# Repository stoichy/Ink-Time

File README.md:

# InkTime - Open Source Smartwatch

InkTime is a low-cost, open-source smartwatch designed for the **EVT (Engineering Validation Test)** phase. This project involves the full hardware design cycle, from schematic capture and PCB layout in Autodesk Fusion 360 to mechanical integration and manufacturing file generation.

## Project Overview

The system architecture centers around the **nRF52840** (Nordic Semiconductor) for BLE connectivity and ultra-low power consumption, paired with a high-contrast E-Paper display.

### Key Features
- **MCU:** Nordic nRF52840 (Cortex-M4 + BLE 5.0).
- **Display:** 1.54" E-Paper (Ultra-low power, sunlight readable).
- **Power:** USB-C charging with 180mAh LiPo battery.
- **Form Factor:** Compact design ready for mechanical integration.

---

## System Architecture

### Block Diagram

The core of the device integrates high-speed SPI for the display and I2C for peripheral sensors.

### Hardware Functionality
- **Microcontroller:** The nRF52840 provides a 2.4GHz radio and ARM® Cortex®-M4 processor.
- **Interfaces:**
  - **SPI:** Dedicated for the E-Ink display to ensure high-speed data transfer.
  - **I2C:** Connects the IMU (Inertial Measurement Unit) and Fuel Gauge for battery monitoring.
  - **GPIO:** Used for tactile buttons and the haptic shaker motor (PWM controlled).
- **Power System:** Charged via USB-C (5V), regulated to 3.3V via a low-dropout (LDO) regulator.

---

## Bill of Materials (BOM)

| Component | Value/Model | Package | Provider (JLC) | Datasheet |
| :--- | :--- | :--- | :--- | :--- |
| **MCU** | nRF52840a | QFN™73 | [JLC Part](https://jlcpcb.com/) | [Link](https://infocenter.nordicsemi.com/pdf/nRF52840_PS_v1.1.pdf) |
| **Display** | E-Paper 1.54" | FPC | [JLC Part](https://jlcpcb.com/) | [Link](#) |
| **Charger IC** | MCP73832 | SOT-23-5 | [JLC Part](https://jlcpcb.com/) | [Link](https://ww1.microchip.com/downloads/en/DeviceDoc/20001984g.pdf) |
| **Battery** | LiPo 180mAh | Custom | N/A | [Link](#) |
| **LDO** | 3.3V Regulator | SOT-23 | [JLC Part](https://jlcpcb.com/) | [Link](#) |

---

## Pinout Mapping

| nRF52840 Pin | Function | Description |
| :--- | :--- | :--- |
| **P0.xx** | SPI_SCK | Serial Clock for E-Ink |
| **P0.yy** | SPI_MOSI | Master Out Slave In for E-Ink |
| **P0.zz** | I2C_SDA | Data line for Sensors |
| **P0.ww** | PWM_VIB | Haptic motor control |

---

## Energy Budget

- **Battery Capacity:** 180 mAh.
- **Deep Sleep Mode:** Estimated < 50 µA.
- **Active Refresh:** ~8-12 mA (peak during E-Ink refresh).
- **Estimated Standby:** Approx. 10-14 days.

---

## Design Log & Constraints

### PCB Implementation
- **Layers:** 2-layer design (Top/Bottom) with dedicated ground planes.
- **Trace Widths:** Power (0.3mm), Signal (0.15mm) to comply with JLC manufacturing standards.
- **Decoupling:** 100nF capacitors (0201) placed close to MCU VCC pins.

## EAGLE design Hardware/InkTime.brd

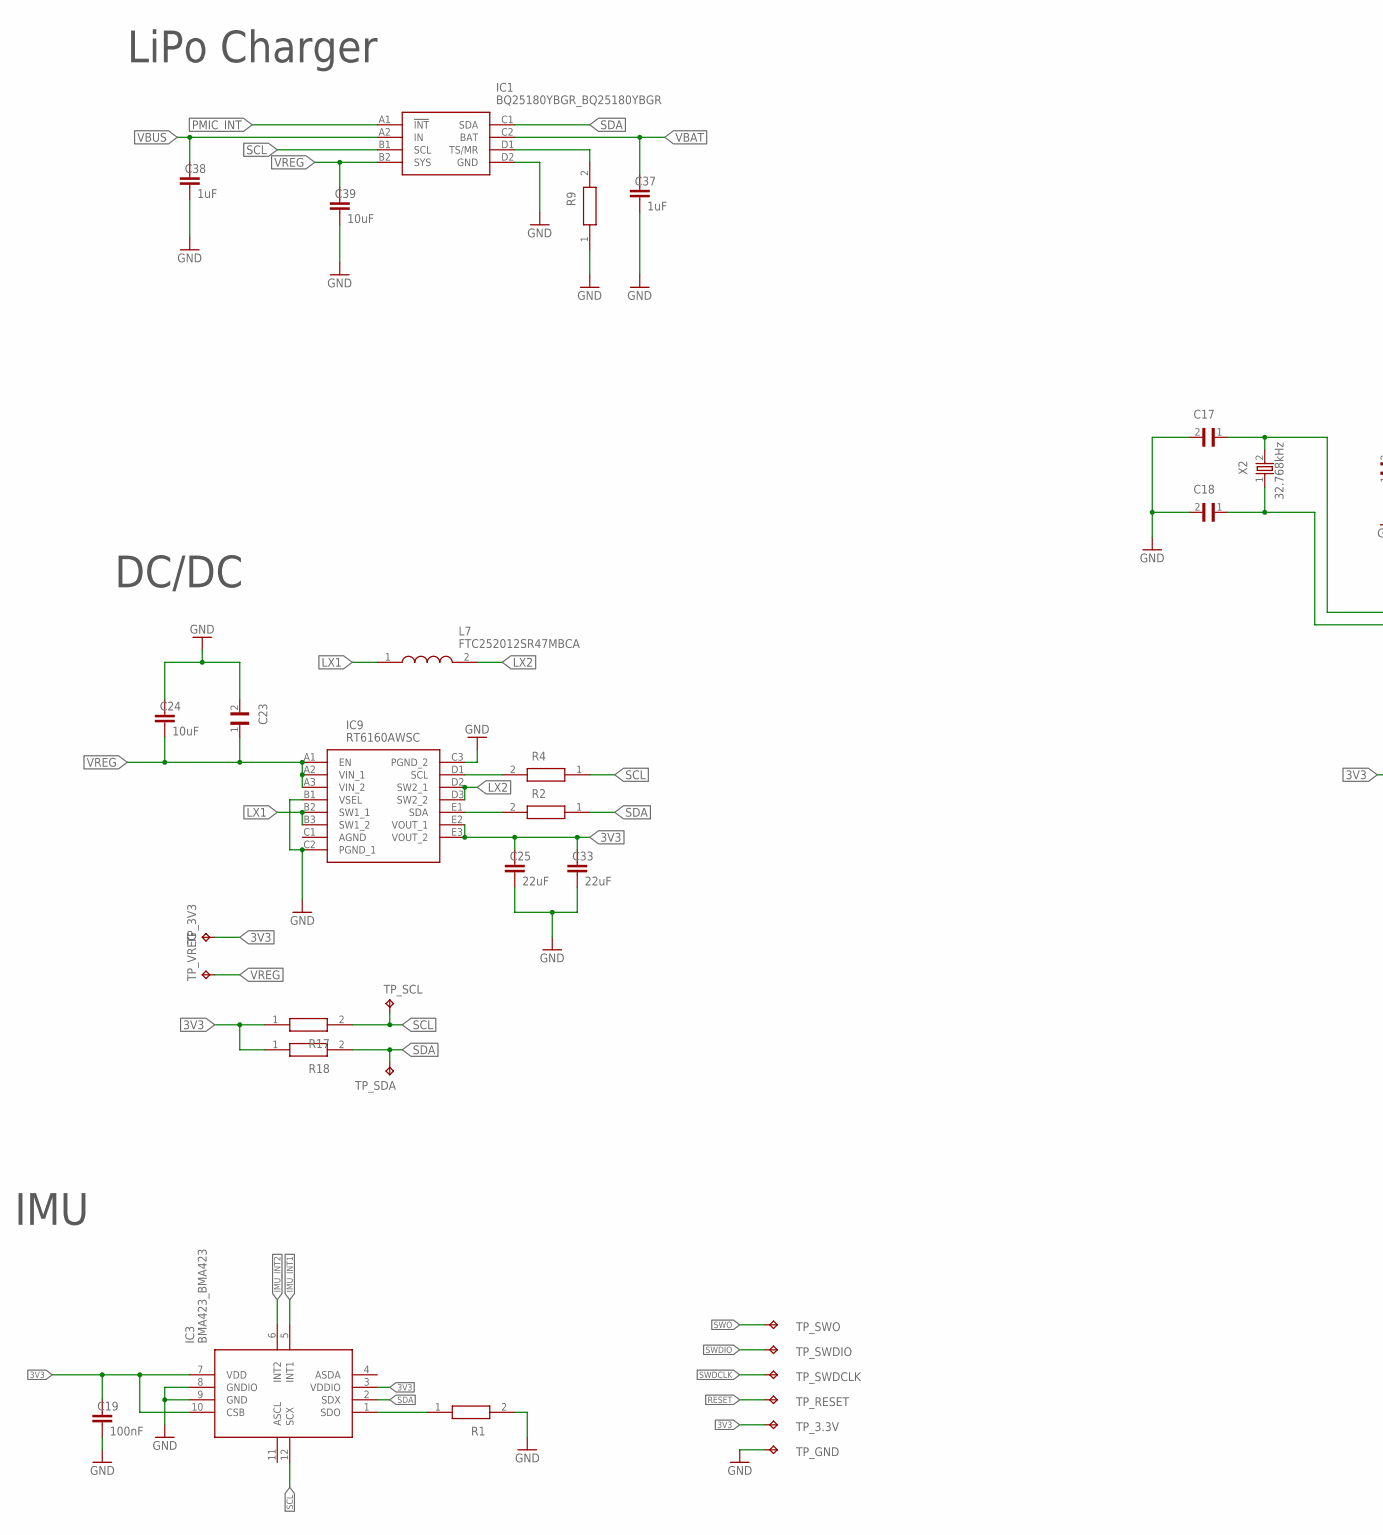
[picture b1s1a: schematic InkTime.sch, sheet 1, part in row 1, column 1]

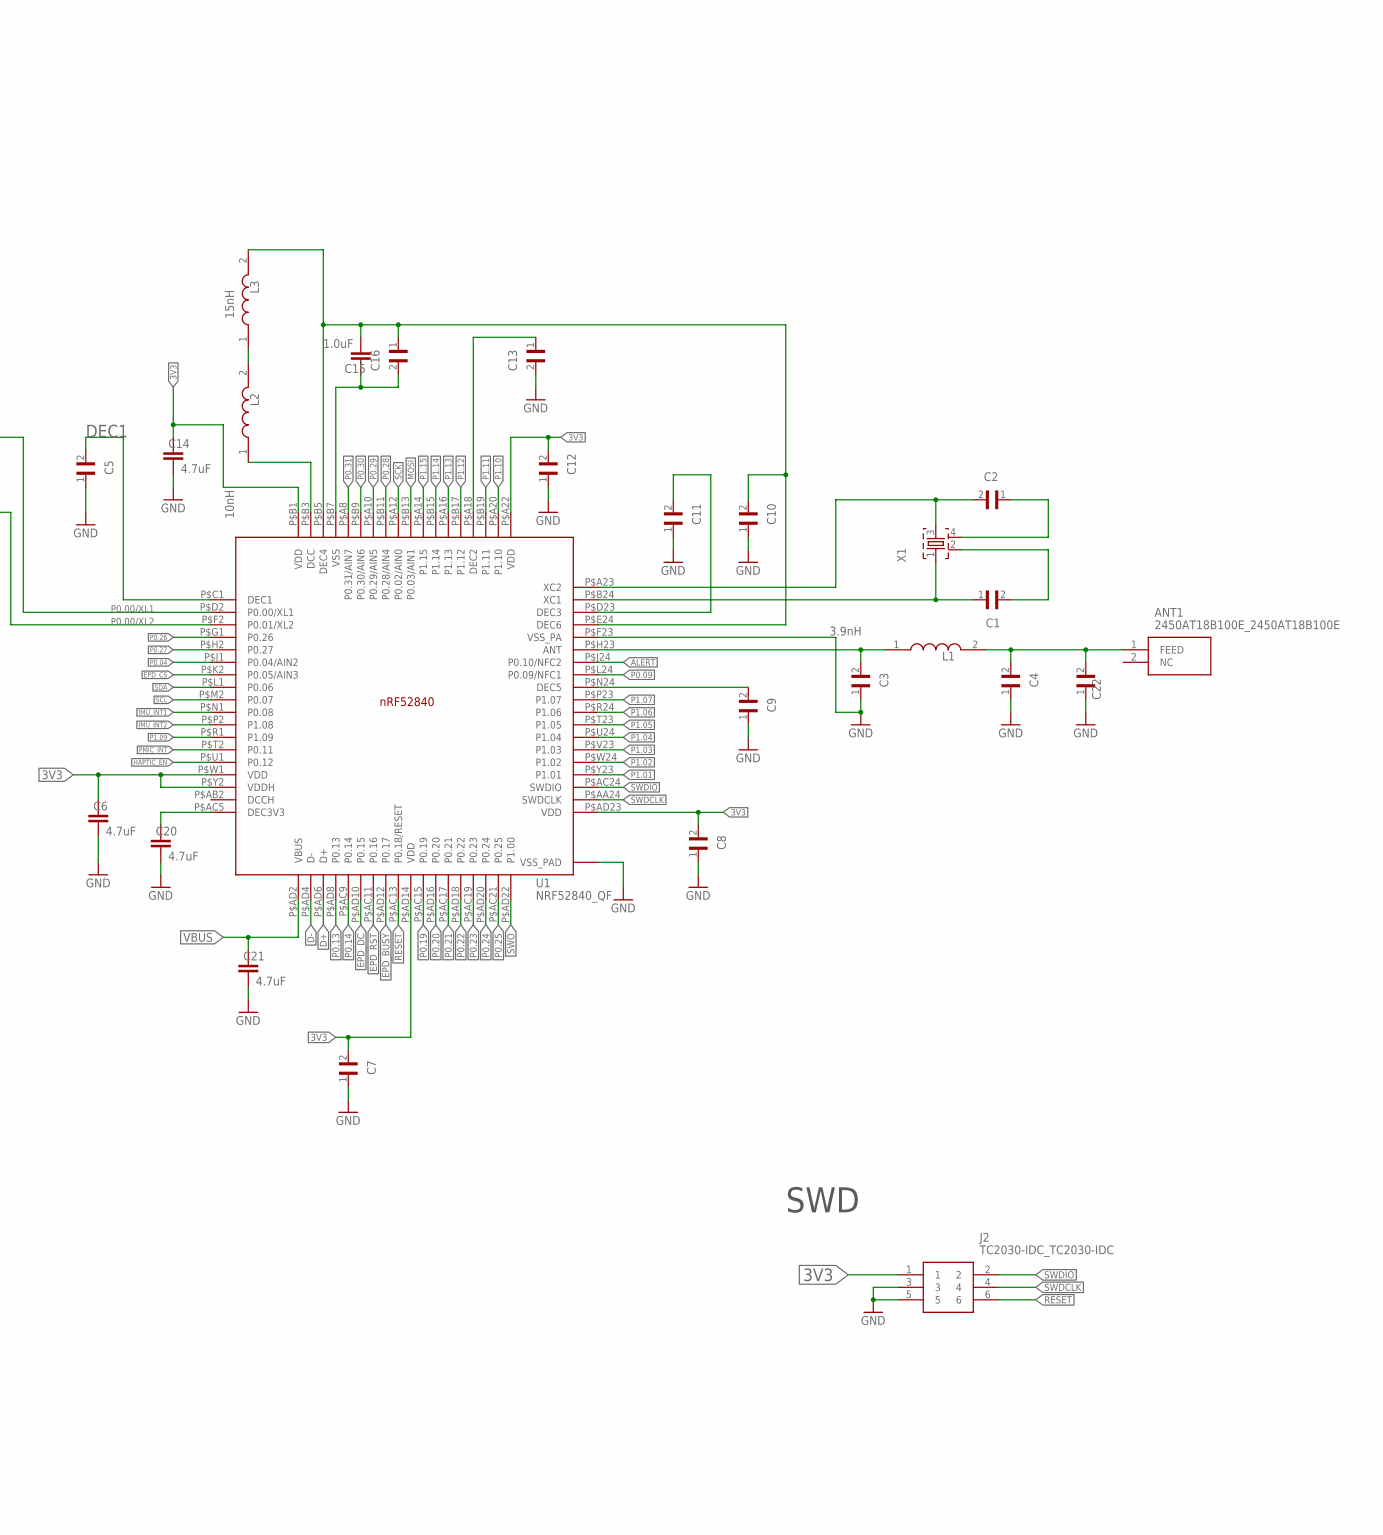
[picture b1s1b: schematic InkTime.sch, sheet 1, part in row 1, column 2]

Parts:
ANT1: 2450AT18B100E_2450AT18B100E; 2450AT18B100E_ANTC3216X140N
C1, C2, C17, C18: 12pF; GRM011R60J152KE01L_2_CAPC0201X13N
C3, C4: 1pF; GRM011R60J152KE01L_2_CAPC0201X13N
C5, C7, C8, C12: 100nF; GRM011R60J152KE01L_2_CAPC0201X13N
C6, C14, C20, C21: 4.7uF; NORDIC_NRF_3_RESC0402_N
C9: 820pF; GRM011R60J152KE01L_2_CAPC0201X13N
C10, C13, C22: N.C.; GRM011R60J152KE01L_2_CAPC0201X13N
C11: 100pF; GRM011R60J152KE01L_2_CAPC0201X13N
C15: 1.0uF; NORDIC_NRF_3_RESC0402_N
C16: 47nF; GRM011R60J152KE01L_2_CAPC0201X13N
C19: 100nF; NORDIC_NRF_3_RESC0402_N
C23: 0.1uF; GRM011R60J152KE01L_2_CAPC0201X13N
C24, C39: 10uF; NORDIC_NRF_3_RESC0402_N
C25, C33: 22uF; NORDIC_NRF_3_RESC0402_N
C37, C38: 1uF; NORDIC_NRF_3_RESC0402_N
IC1: BQ25180YBGR_BQ25180YBGR; BQ25180YBGR_BGA8C40P2X4_100X155X50
IC3: BMA423_BMA423
IC9: RT6160AWSC; RT6160AWSC_BGA15C40P3X5_140X230X60
J2: TC2030-IDC_TC2030-IDC; TC2030-IDC_TC2030IDC
L1: 3.9nH; MLP2016SR47MT0S1_INDC2016X100N
L2: 10nH; MLP2016SR47MT0S1_INDC2016X100N
L3: 15nH; MLP2016SR47MT0S1_INDC2016X100N
L7: FTC252012SR47MBCA; MLP2016SR47MT0S1_INDC2016X100N
R1, R2, R4: 0; ERA-1AEB3401C_0201
R9: 10k; ERA-1AEB3401C_0201
R17: 3k3; ERA-1AEB3401C_0201
R18: 3K3; ERA-1AEB3401C_0201
TP_3.3V, TP_3V3: HECTOR_WATCH_1_TPTP20R; HECTOR_WATCH_1_TP20R
TP_GND: HECTOR_WATCH_1_TPTP20R; HECTOR_WATCH_1_TP20R
TP_RESET: HECTOR_WATCH_1_TPTP20R; HECTOR_WATCH_1_TP20R
TP_SCL: HECTOR_WATCH_1_TPTP20R; HECTOR_WATCH_1_TP20R
TP_SDA: HECTOR_WATCH_1_TPTP20R; HECTOR_WATCH_1_TP20R
TP_SWDCLK: HECTOR_WATCH_1_TPTP20R; HECTOR_WATCH_1_TP20R
TP_SWDIO: HECTOR_WATCH_1_TPTP20R; HECTOR_WATCH_1_TP20R
TP_SWO: HECTOR_WATCH_1_TPTP20R; HECTOR_WATCH_1_TP20R
TP_VREG: HECTOR_WATCH_1_TPTP20R; HECTOR_WATCH_1_TP20R
U1: NRF52840_QF; NORDIC_NRF_4_AQFN50P700X700X85_HS-74N
X1: NORDIC_NRF_XTAL_32MHZ; NORDIC_NRF_BT-XTAL_2016_N
X2: 32.768kHz; NORDIC_NRF_1_XTAL_3215_N

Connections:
3V3: C6.1, C7.2, C8.2, C12.2, C14.1, C19.1, C25.1, C33.1, IC3.3 (VDDIO), IC3.7 (VDD), IC3.10 (CSB), IC9.E2 (VOUT_1), IC9.E3 (VOUT_2), J2.1, R17.1, R18.1, TP_3.3V.TP, TP_3V3.TP, U1.P$A22 (VDD), U1.P$AD14 (VDD), U1.P$AD23 (VDD), U1.P$B1 (VDD), U1.P$W1 (VDD), U1.P$Y2 (VDDH); also elsewhere on the board
ALERT: U1.P$J24 (P0.10/NFC2); also elsewhere on the board
D+: U1.P$AD6 (D+); also elsewhere on the board
D-: U1.P$AD4 (D-); also elsewhere on the board
DEC1: C5.2, U1.P$C1 (DEC1)
EPD_BUSY: U1.P$AD12 (P0.17); also elsewhere on the board
EPD_CS: U1.P$K2 (P0.05/AIN3); also elsewhere on the board
EPD_DC: U1.P$AD10 (P0.15); also elsewhere on the board
EPD_RST: U1.P$AC11 (P0.16); also elsewhere on the board
GND: C3.1, C4.1, C5.1, C6.2, C7.1, C8.1, C9.1, C10.1, C11.1, C12.1, C13.2, C14.2, C17.2, C18.2, C19.2, C20.2, C21.2, C22.1, C23.2, C24.1, C25.2, C33.2, C37.2, C38.2, C39.2, IC1.D2 (GND), IC3.8 (GNDIO), IC3.9 (GND), IC9.B1 (VSEL), IC9.C2 (PGND_1), IC9.C3 (PGND_2), J2.3, J2.5, R1.2, R9.1, TP_GND.TP, U1.P$74 (VSS_PAD), U1.P$75 (VSS_PAD), U1.P$76 (VSS_PAD), U1.P$77 (VSS_PAD), U1.P$78 (VSS_PAD), U1.P$79 (VSS_PAD), U1.P$80 (VSS_PAD), U1.P$81 (VSS_PAD), U1.P$82 (VSS_PAD), U1.P$83 (VSS_PAD), U1.P$84 (VSS_PAD), U1.P$85 (VSS_PAD), U1.P$86 (VSS_PAD), U1.P$87 (VSS_PAD), U1.P$88 (VSS_PAD), U1.P$89 (VSS_PAD), U1.P$90 (VSS_PAD), U1.P$F23 (VSS_PA); also elsewhere on the board
HAPTIC_EN: U1.P$U1 (P0.12); also elsewhere on the board
IMU_INT1: IC3.5 (INT1), U1.P$N1 (P0.08)
IMU_INT2: IC3.6 (INT2), U1.P$P2 (P1.08)
LX1: IC9.B2 (SW1_1), IC9.B3 (SW1_2), L7.1
LX2: IC9.D2 (SW2_1), IC9.D3 (SW2_2), L7.2
MOSI: U1.P$B13 (P0.03/AIN1); also elsewhere on the board
unnamed: C20.1, U1.P$AC5 (DEC3V3)
unnamed: IC1.D1 (TS/MR), R9.2
unnamed: C9.2, U1.P$N24 (DEC5)
unnamed: C3.2, L1.1, U1.P$H23 (ANT)
unnamed: IC9.D1 (SCL), R4.2
unnamed: ANT1.1 (FEED), C4.2, C22.2, L1.2
unnamed: IC9.E1 (SDA), R2.2
unnamed: C10.2, C15.2, C16.1, L3.2, U1.P$B5 (DEC4), U1.P$E24 (DEC6)
unnamed: IC3.1 (SDO), R1.1
unnamed: C11.2, U1.P$D23 (DEC3)
unnamed: C2.2, U1.P$A23 (XC2), X1.3
unnamed: C2.1, X1.4
unnamed: C1.2, X1.2
unnamed: C1.1, U1.P$B24 (XC1), X1.1
unnamed: L2.2, L3.1
unnamed: C13.1, U1.P$A18 (DEC2)
unnamed: C15.1, C16.2, U1.P$B7 (VSS)
unnamed: L2.1, U1.P$B3 (DCC)
P0.00/XL1: C17.1, U1.P$D2 (P0.00/XL1), X2.2
P0.00/XL2: C18.1, U1.P$F2 (P0.01/XL2), X2.1
P0.04: U1.P$J1 (P0.04/AIN2)
P0.09: U1.P$L24 (P0.09/NFC1)
P0.13: U1.P$AD8 (P0.13); also elsewhere on the board
P0.14: U1.P$AC9 (P0.14); also elsewhere on the board
P0.19: U1.P$AC15 (P0.19)
P0.20: U1.P$AD16 (P0.20)
P0.21: U1.P$AC17 (P0.21)
P0.22: U1.P$AD18 (P0.22)
P0.23: U1.P$AC19 (P0.23)
P0.24: U1.P$AD20 (P0.24)
P0.25: U1.P$AC21 (P0.25)
P0.26: U1.P$G1 (P0.26)
P0.27: U1.P$H2 (P0.27)
P0.28: U1.P$B11 (P0.28/AIN4)
P0.29: U1.P$A10 (P0.29/AIN5)
P0.30: U1.P$B9 (P0.30/AIN6)
P0.31: U1.P$A8 (P0.31/AIN7)
P1.01: U1.P$Y23 (P1.01); also elsewhere on the board
P1.02: U1.P$W24 (P1.02); also elsewhere on the board
P1.03: U1.P$V23 (P1.03)
P1.04: U1.P$U24 (P1.04)
P1.05: U1.P$T23 (P1.05)
P1.06: U1.P$R24 (P1.06)
P1.07: U1.P$P23 (P1.07)
P1.09: U1.P$R1 (P1.09)
P1.10: U1.P$A20 (P1.10)
P1.11: U1.P$B19 (P1.11)
P1.12: U1.P$B17 (P1.12)
P1.13: U1.P$A16 (P1.13)
P1.14: U1.P$B15 (P1.14)
P1.15: U1.P$A14 (P1.15)
PMIC_INT: IC1.A1 (!INT), U1.P$T2 (P0.11)
RESET: J2.6, TP_RESET.TP, U1.P$AC13 (P0.18/RESET); also elsewhere on the board
SCK: U1.P$A12 (P0.02/AIN0); also elsewhere on the board
SCL: IC1.B1 (SCL), IC3.12 (SCX), R4.1, R17.2, TP_SCL.TP, U1.P$M2 (P0.07); also elsewhere on the board
SDA: IC1.C1 (SDA), IC3.2 (SDX), R2.1, R18.2, TP_SDA.TP, U1.P$L1 (P0.06); also elsewhere on the board
SWDCLK: J2.4, TP_SWDCLK.TP, U1.P$AA24 (SWDCLK)
SWDIO: J2.2, TP_SWDIO.TP, U1.P$AC24 (SWDIO)
SWO: TP_SWO.TP, U1.P$AD22 (P1.00)
VBAT: C37.1, IC1.C2 (BAT); also elsewhere on the board
VBUS: C21.1, C38.1, IC1.A2 (IN), U1.P$AD2 (VBUS); also elsewhere on the board
VREG: C23.1, C24.2, C39.1, IC1.B2 (SYS), IC9.A1 (EN), IC9.A2 (VIN_1), IC9.A3 (VIN_2), TP_VREG.TP

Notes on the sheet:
DC/DC
LiPo Charger
IMU
SWD

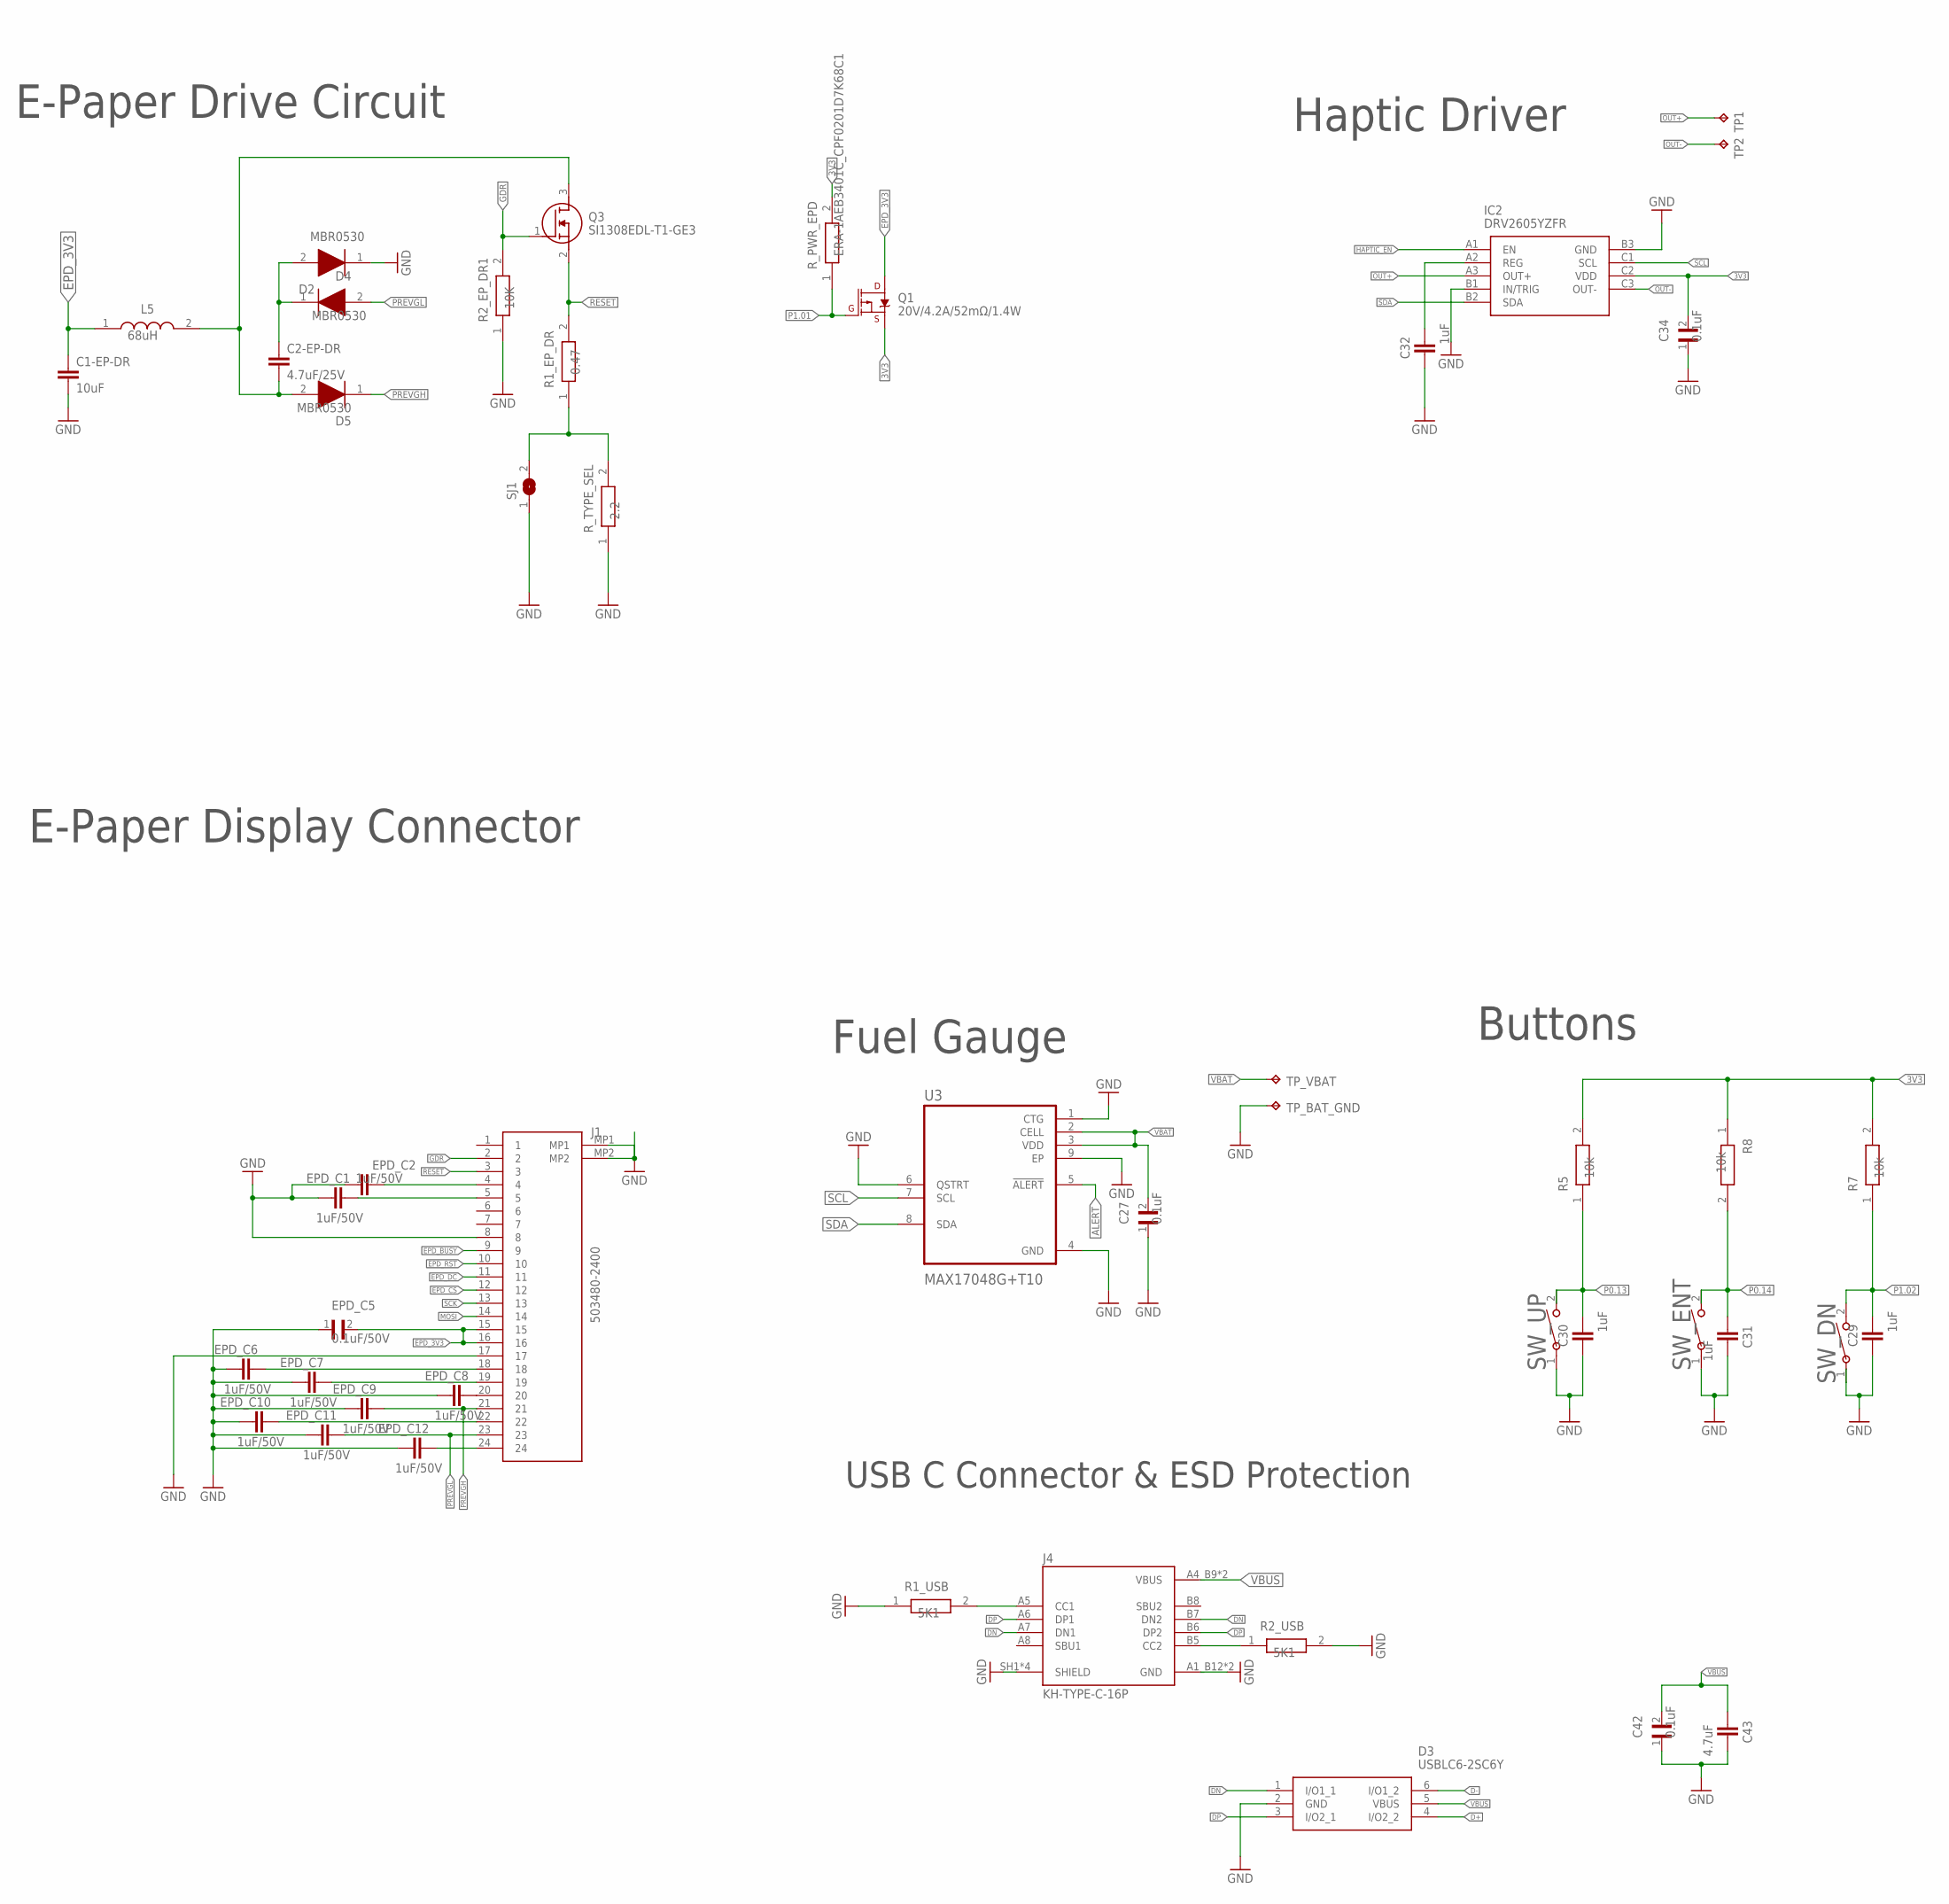
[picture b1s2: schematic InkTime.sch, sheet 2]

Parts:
C1-EP-DR: 10uF; NORDIC_NRF_3_RESC0402_N
C2-EP-DR: 4.7uF/25V; NORDIC_NRF_3_RESC0402_N
C27, C34, C42: 0.1uF; GRM011R60J152KE01L_2_CAPC0201X13N
C29, C30, C31, C32: 1uF; NORDIC_NRF_3_RESC0402_N
C43: 4.7uF; NORDIC_NRF_3_RESC0402_N
D2, D4, D5: MBR0530; ESP32_C6_LIBRARY_5_SOD3716X135N
D3: USBLC6-2SC6Y; ESP32_C6_LIBRARY_3_SOT95P280X145-6N
EPD_C1, EPD_C2, EPD_C6, EPD_C7, EPD_C8, EPD_C9, EPD_C10, EPD_C11, EPD_C12: 1uF/50V; NORDIC_NRF_3_RESC0402_N
EPD_C5: 0.1uF/50V; GRM011R60J152KE01L_2_CAPC0201X13N
IC2: DRV2605YZFR; DRV2605YZFR_BGA9C50P3X3_144X144X62
J1: 503480-2400; 503480-2400_5034802400
J4: KH-TYPE-C-16P; KH-TYPE-C-16P_KINGHELM_KH-TYPE-C-16P
L5: 68uH; MLP2016SR47MT0S1_INDC2016X100N
Q1: 20V/4.2A/52mΩ/1.4W; ESP32_C6_LIBRARY_4_ESP32_C6_LIBRARY_4_ESP32_C6_LIBRARY_4_ES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
Q3: SI1308EDL-T1-GE3; ESP32_C6_LIBRARY_6_SOT65P210X110-3N
R1_EP_DR: 0.47; ERA-1AEB3401C_0201
R1_USB, R2_USB: 5K1; ERA-1AEB3401C_0201
R2_EP_DR1: 10K; ERA-1AEB3401C_0201
R5, R7, R8: 10k; ERA-1AEB3401C_0201
R_PWR_EPD: ERA-1AEB3401C_CPF0201D7K68C1; ERA-1AEB3401C_0201
R_TYPE_SEL: 2.2; ERA-1AEB3401C_0201
SJ1: ESP32_C6_LIBRARY_7_JUMPER_SJ
SW_DN: 2025-10-22_07-23-44_LIBRARY_EVP-AKE31ASW_EVP-AKE3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; 2025-10-22_07-23-44_LIBRARY_SW_EVP-AKE31A_PAN
SW_ENT: 2025-10-22_07-23-44_LIBRARY_EVP-AKE31ASW_EVP-AKE3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; 2025-10-22_07-23-44_LIBRARY_SW_EVP-AKE31A_PAN
SW_UP: 2025-10-22_07-23-44_LIBRARY_EVP-AKE31ASW_EVP-AKE3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; 2025-10-22_07-23-44_LIBRARY_SW_EVP-AKE31A_PAN
TP1, TP2: HECTOR_WATCH_1_TPTP20R; HECTOR_WATCH_1_TP20R
TP_BAT_GND: HECTOR_WATCH_1_TPTP20R; HECTOR_WATCH_1_TP20R
TP_VBAT: HECTOR_WATCH_1_TPTP20R; HECTOR_WATCH_1_TP20R
U3: MAX17048G+T10; ESP32_C6_LIBRARY_SON50P200X200X80-9N

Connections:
3V3: C34.2, IC2.C2 (VDD), Q1.2 (S), R5.2, R7.2, R8.1, R_PWR_EPD.2; also elsewhere on the board
ALERT: U3.5 (!ALERT); also elsewhere on the board
D+: D3.4 (I/O2_2); also elsewhere on the board
D-: D3.6 (I/O1_2); also elsewhere on the board
DN: D3.1 (I/O1_1), J4.A7 (DN1), J4.B7 (DN2)
DP: D3.3 (I/O2_1), J4.A6 (DP1), J4.B6 (DP2)
EPD_3V3: C1-EP-DR.1, EPD_C5.2, J1.15, J1.16, L5.1, Q1.3 (D)
EPD_BUSY: J1.9; also elsewhere on the board
EPD_CS: J1.12; also elsewhere on the board
EPD_DC: J1.11; also elsewhere on the board
EPD_RST: J1.10; also elsewhere on the board
GDR: J1.2, Q3.1 (G), R2_EP_DR1.2
GND: C1-EP-DR.2, C27.1, C29.1, C30.1, C31.2, C32.1, C34.1, C42.1, C43.2, D3.2 (GND), D4.1 (K), EPD_C1.1, EPD_C2.1, EPD_C5.1, EPD_C6.1, EPD_C7.1, EPD_C8.1, EPD_C9.1, EPD_C10.1, EPD_C11.1, EPD_C12.1, IC2.B1 (IN/TRIG), IC2.B3 (GND), J1.8, J1.17, J1.MP1, J1.MP2, J4.A1_B12 (GND), J4.A12_B1 (GND), J4.SH1 (SHIELD), J4.SH2 (SHIELD), J4.SH3 (SHIELD), J4.SH4 (SHIELD), R1_USB.1, R2_EP_DR1.1, R2_USB.2, R_TYPE_SEL.1, SJ1.1, SW_DN.1, SW_ENT.1, SW_UP.1, TP_BAT_GND.TP, U3.1 (CTG), U3.4 (GND), U3.6 (QSTRT), U3.9 (EP); also elsewhere on the board
HAPTIC_EN: IC2.A1 (EN); also elsewhere on the board
MOSI: J1.14; also elsewhere on the board
unnamed: C2-EP-DR.2, D5.2 (A), L5.2, Q3.3 (D)
unnamed: C2-EP-DR.1, D2.1 (K), D4.2 (A)
unnamed: R1_EP_DR.1, R_TYPE_SEL.2, SJ1.2
unnamed: J4.A5 (CC1), R1_USB.2
unnamed: EPD_C2.2, J1.4
unnamed: EPD_C1.2, J1.5
unnamed: EPD_C6.2, J1.18
unnamed: EPD_C7.2, J1.19
unnamed: EPD_C8.2, J1.20
unnamed: C32.2, IC2.A2 (REG)
unnamed: EPD_C10.2, J1.22
unnamed: EPD_C12.2, J1.24
unnamed: J4.B5 (CC2), R2_USB.1
OUT+: IC2.A3 (OUT+), TP1.TP
OUT-: IC2.C3 (OUT-), TP2.TP
P0.13: C30.2, R5.1, SW_UP.2; also elsewhere on the board
P0.14: C31.1, R8.2, SW_ENT.2; also elsewhere on the board
P1.01: Q1.1 (G), R_PWR_EPD.1; also elsewhere on the board
P1.02: C29.2, R7.1, SW_DN.2; also elsewhere on the board
PREVGH: D5.1 (K), EPD_C9.2, J1.21
PREVGL: D2.2 (A), EPD_C11.2, J1.23
RESET: J1.3, Q3.2 (S), R1_EP_DR.2; also elsewhere on the board
SCK: J1.13; also elsewhere on the board
SCL: IC2.C1 (SCL), U3.7 (SCL); also elsewhere on the board
SDA: IC2.B2 (SDA), U3.8 (SDA); also elsewhere on the board
VBAT: C27.2, TP_VBAT.TP, U3.2 (CELL), U3.3 (VDD); also elsewhere on the board
VBUS: C42.2, C43.1, D3.5 (VBUS), J4.A4_B9 (VBUS), J4.A9_B4 (VBUS); also elsewhere on the board

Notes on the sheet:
E-Paper Drive Circuit
E-Paper Display Connector
Fuel Gauge
USB C Connector & ESD Protection
Buttons
Haptic Driver

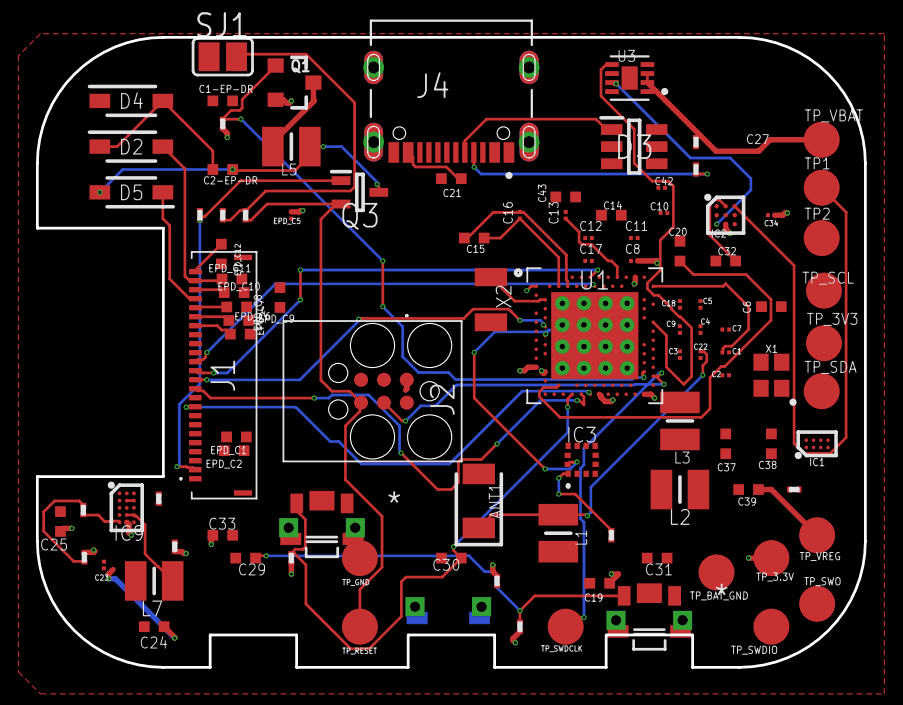
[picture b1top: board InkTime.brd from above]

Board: 4 copper layers, 46.0 x 35.0 mm, 105 parts (1 on the bottom side), 72 nets.

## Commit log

2026-04-10 Add Fusion Project
    Added all project files into the repository, including some screenshots
2026-04-10 Add README and Diagram
    Added a Block Diagram that shows all of the watch components and changed README in order to present details of implementation.
2026-04-10 Change Diagram
    Changed Block Diagram to be more descriptive and intuitive
2026-04-10 Change Image details
    Further simplified diagram components descriptions
2026-04-18 Corrected schematic layout within frame
    Added a standard frame and aligned components to the sheet origin. Fixes #1
2026-04-18 Update Schematic.sch
    Fixed the values of the following components:
    - ANT1
    - IC3
    - IC1
    - J2
    Please let me know if there are any other incorrect values by opening another issue.
2026-04-18 Fix added wire
    Removed added wire on MP1 pin of J1 component.
    Fixes #5
2026-04-18 Display resistors and capacitor value
    Displayed the values of resistors and capacitors so as to ensure a more readable schematic.
2026-04-18 Revert "Display resistors and capacitor value"
    This reverts commit e3d6df2a964783730cc62ca4a1df47b7156c4929.
2026-04-18 Display resistors and capacitor value
    Displayed the values of resistors and capacitors so as to ensure a more readable schematic.
    Fixes #7
2026-04-18 Fix copper wire position
    Completely overhauled the PCB routing design so as to separate the antenna from the rest of the layout.
    Fixes #8
2026-04-18 Overhaul Silkscreen readability
    Changed all components names in the layout into smaller and more readable versions.
    Fixes #12
2026-04-21 Add 3D Models for all components
    Added 3d Components for all PCB components along with different perspectives for the shell of the watch. Also fixed several issues with the layout.
    Fixes #13
2026-04-21 Replace PCB image with 3D isometric version
    Updated PCB layout image to 3D isometric view.
2026-04-21 Remove EVT status section from README
    Removed EVT status notes from the README.

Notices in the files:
parts and their libraries:
COPYRIGHT: Copyright (C) 2025 Ultra Librarian. All rights reserved.
